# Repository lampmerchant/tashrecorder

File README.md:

# TashRecorder

## Elevator Pitch

It's an audio interface that can be switched between imitating the Farallon MacRecorder, an audio digitizer for vintage Macintosh computers without audio input, and the Apple MIDI Interface, a standard MIDI interface for the Macintosh.  It targets the PIC12F1501 (8 pins, ~$0.96) microcontroller.

## Technical Details

### Connections

```
                      .--------.
              Supply -|01 \/ 08|- Ground
       RxD- <--- RA5 -|02    07|- RA0 <--- MIDI/Audio In
       RxD+ <--- RA4 -|03    06|- RA1 ---> Clock Out
Mode Select ---> RA3 -|04    05|- RA2 ---> LED
                      '--------'
```

Mode Select floats high and selects audio digitizer mode by default; pulling it low selects MIDI interface mode.  The mode can be changed at any time.

The LED output is active high.

### Audio Digitizer Mode

In Audio Digitizer mode, the firmware imitates a Farallon MacRecorder, generating a clock of approximately 358 kHz (one tenth the NTSC color burst frequency), oversampling the input pin at a rate of approximately 44 kHz and transmitting 8-bit samples to the Macintosh at a rate of approximately 22 kHz.

The LED flashes on when the audio has peaked for a set number of consecutive samples (3 by default, changeable by editing the PEAKPWR parameter in firmware).  Peaking is determined by masking off a number of bits (3 by default, changeable by editing the PEAKMSK parameter in firmware) and checking whether the remaining bits are all ones or all zeroes.

### MIDI Interface Mode

In MIDI Interface Mode, the firmware imitates the input of an Apple MIDI Interface, generating a 1 MHz clock (32 times the MIDI baud rate of 31250 Hz) and relaying the input pin's state directly to the RxD pins.  The MIDI input pin's state is inverted before being reflected by the RxD pins; this allows it to be connected directly to the output of an optocoupler such as the 6N138 with the addition of an external pullup resistor.

The LED flashes on when data is being received over the MIDI interface.

### Building Firmware

Building the firmware requires Microchip MPASM, which is included with their development environment, MPLAB.  Note that you **must** use MPLAB X version 5.35 or earlier or MPLAB 8 as later versions of MPLAB X have removed MPASM.

The firmware can also be built using gpasm, an MPASM-compatible assembler that is part of the [gputils](https://gputils.sourceforge.io/) project.  Please note, however, that the release builds are built using MPASM and compatibility with gpasm is not tested.

## Building Your Own

1-Bit Fever Dreams on YouTube has made a helpful [video](https://www.youtube.com/watch?v=QnrPvtYhGZ4) detailing the process of building a TashRecorder using [demik's PCB](https://github.com/lampmerchant/tashrecorder/tree/main/pcb).

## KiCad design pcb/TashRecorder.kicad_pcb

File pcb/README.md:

# TashRecorder

This is a simple (but dense) design, using all through hole components.  It's designed this way to be period correct and easy to build for people who don't like soldering SMT components.

This folder contains the source KiKad files for the main board. Please check the Panels subfolder for the FR-4 front and back plates.

## BOM
### Mandatory

Here is the BOM for the main board. Part number are what was tested on prototypes board but you may find alternatives easily, especially resistors and sockets

| Reference(s)          | Value      | Quantity | Notes                                  | Part number              |
|-----------------------|------------|----------|----------------------------------------|--------------------------|
| C1, 2, 7, 9-10, 12-13 | 100nF      | 7        | ceramic capacitor 5.08mm               | Weltron 453358           |
| C3                    | 6800pF     | 1        | film capacitor 5mm                     | Wima FKS2G016801B00KSSD  |
| C8                    | 680pF      | 1        | film capacitor 5mm                     | Wima FKP2J006801D00HSSD  |
| C4, C5, C8, C11       | 22uF       | 4        | aluminium electrolytic capacitor       | Panasonic ECA-1HHG220I   |
| D1 to D6              | 1N4148     | 6        | general purpose switching diode        | Vishay 1N4148-TAP        |
| D7                    | Red        | 1        | High efficiency 20000-30000mcd 5mm LED | TRU TC-10551696          |
| J1                    | RCA        | 1        | RCA Phono Connector                    | CUI Devices RCJ-013      |
| J2                    | Connector  | 1        | Circular Mini-DIN Connectors 8P        | Kycon KMDGX-8S-AS        |
| MK1                   | Micro      | 1        | omnidirectional electret microphone    | DB Unlimited MO093803-1  |
| R1, R2, R6            | 2.4kΩ      | 3        | standard 0.25W metal film resistor     | TRU MF0W4FF2401          |
| R3, R12               | 1.2kΩ      | 2        | standard 0.25W carbon film resistor    | TRU CFR0W4J0122          |
| R4, R5, R7, R9        | 220kΩ      | 4        | standard 0.25W carbon film resistor    | TRU CFR0W4J0224          |
| R8, R14, R15          | 47Ω        | 3        | standard 0.25W carbon film resistor    | TRU CFR0W4J0470          |
| R10                   | 4.7kΩ      | 1        | standard 0.25W carbon film resistor    | TRU CFR0W4J0472          |
| R11                   | 10kΩ       | 1        | standard 0.25W carbon film resistor    | TRU CFR0W4J0103          |
| RV1                   | 100kΩ      | 1        | audio 100kΩ panel potentiometer        | Bourns PTD901-2015K-A104 |
| SW1                   | SPDT       | 1        | slide switches right angle             | E-Switch EG1224          |
| U1, U2                | 2.5V       | 2        | 2.5V TO-92-3 20mA voltage reference    | ON Semi LM385Z-2.5       |
| U3                    | OPA2337    | 1        | low power RR out CMOS op-amp           | Texas OPA2337PA          |
| U4                    | PIC        | 1        | 8-bit Microcontrollers DIP PIC12F1501  | MC PIC12F1501-I/P        |
| Case                  | ABS        | 1        | Instrument Case, ABS 2.6x2.6"          | HM 1593K(TBU\|GY\|BK)    |
| PCB Screws            | #4         | 4        | Phillips Pan Head screws #4 x 1/4"     | SERPAC 6004              |
| Socket                | DIP-8      | 2        | DIP-8 socket                           | TRU TC-A 08-LC-TT-203    |
| Knob                  | Blue       | 1        | knob for Ø 6 mm 18 teeth shafts        | PSP 49009-BL             |

Using sockets is recommended because it will allow you to reclaim the microcontroler and op-amp. This will also allow you to upgrade the firmware if a future firmware is released.

### BOM (external links)
Here is a complete mouser. It includes lots of 10 when that was cheaper. You may have extra components
- https://www.mouser.fr/ProjectManager/ProjectDetail.aspx?AccessID=31409f3429

## PCBs
Main PCB is 4 layers. Panels are simple 2 layers boards. The gerbers are avaible in the release section.
Check for the following files:
* TashRecorder_2.1.zip: main board revision 2.1
* TashRecorder_back_panel_2.1.zip: FR-4 back panel revision 2.1
* TashRecorder_front_panel_2.1.zip: FR-4 front panel revision 2.1

You should be use any mainstream PCB manufacturer for theses. Nothing special about them. PCB thickness should be 1.6mm

On JLCPCB, select "Specify a location" to the option "Remove Order Number" for all of them

## Building
Building is straightworfard. It's recommended to start with small components first (diodes, then resistor, LED), then other components, and connectors last.
For Japanase mounted resistors, the resistor will go on the circle side

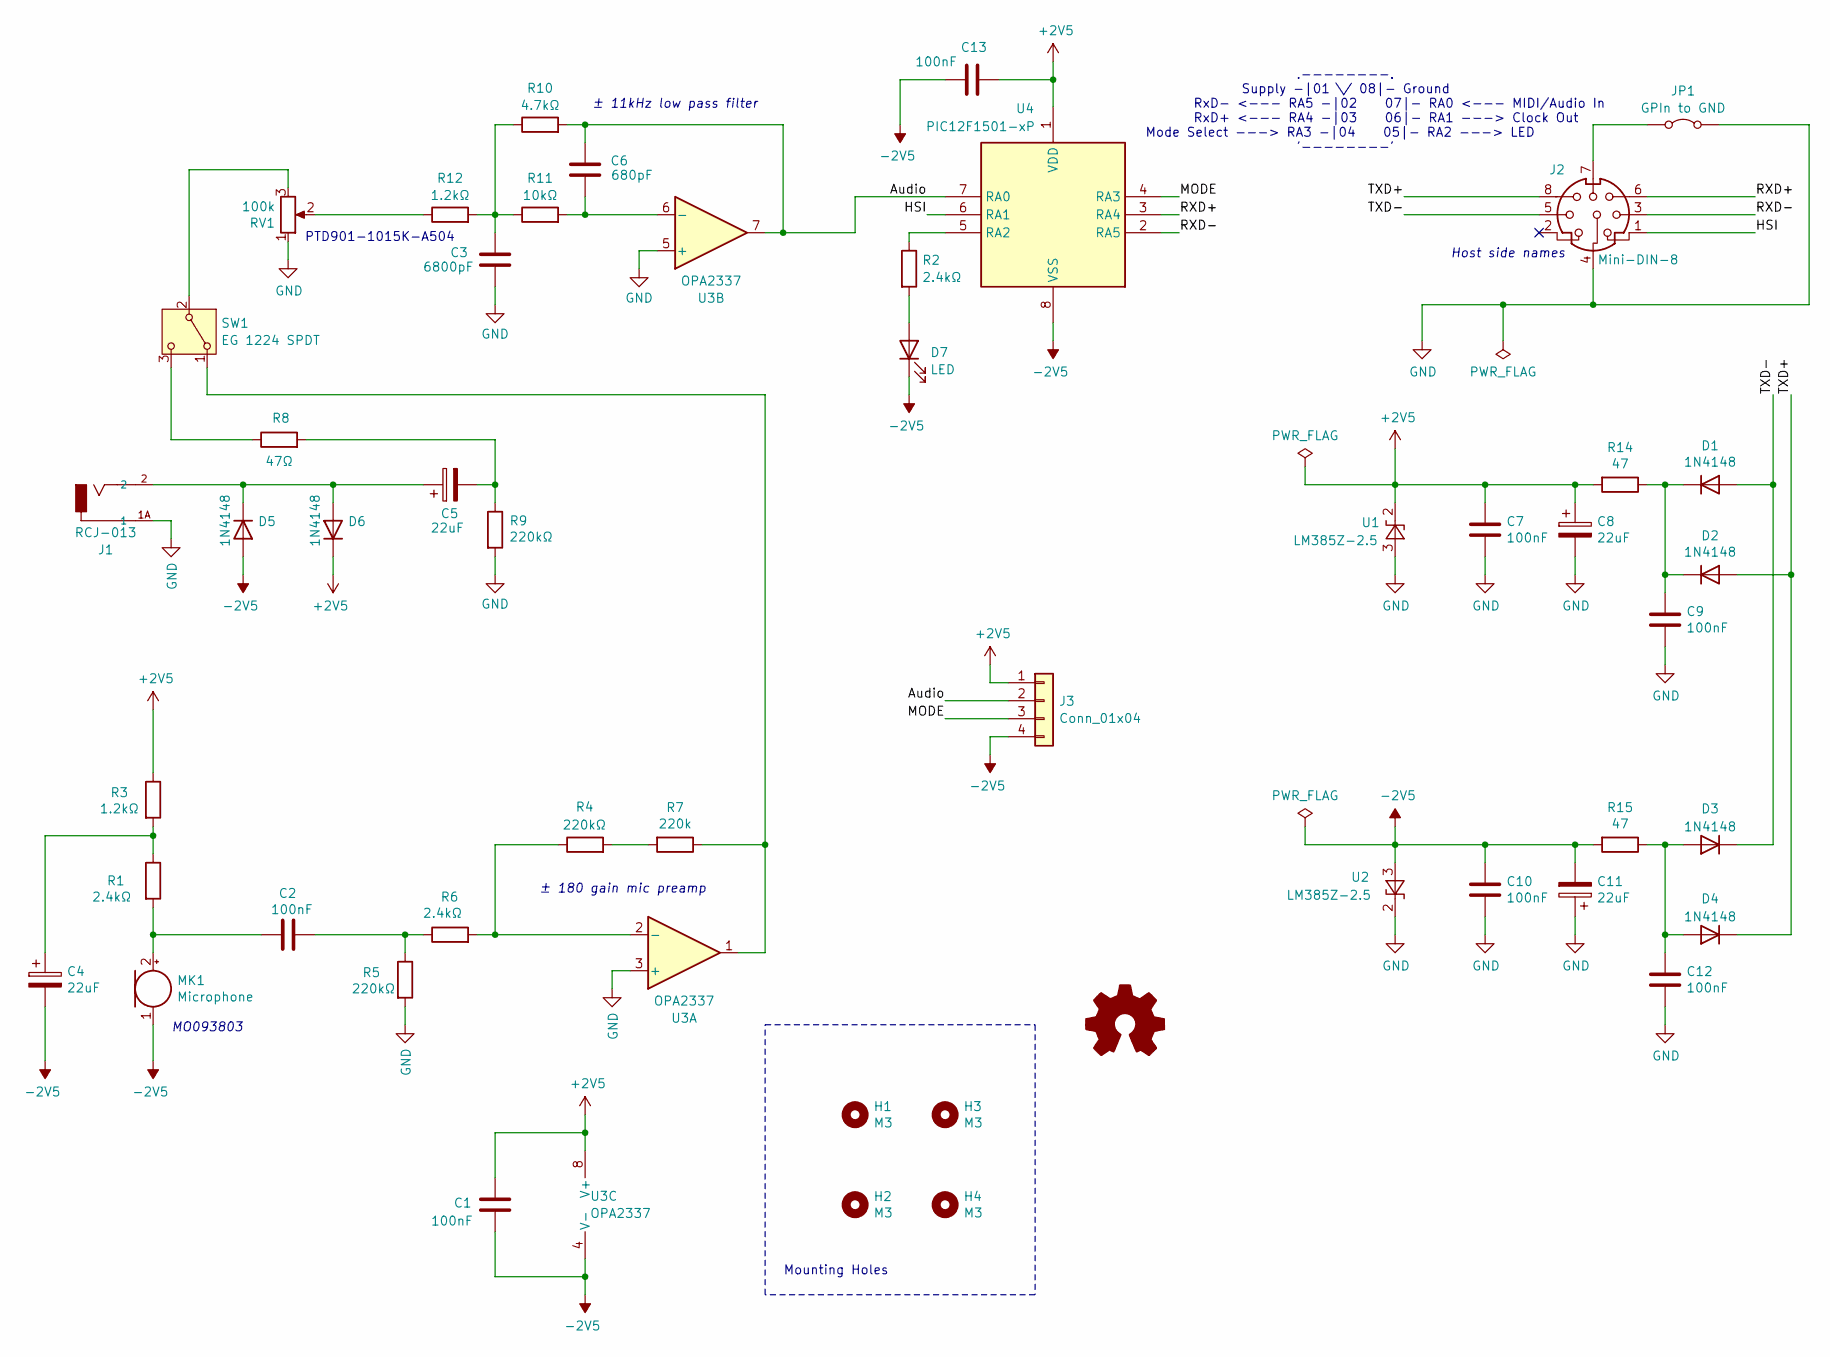
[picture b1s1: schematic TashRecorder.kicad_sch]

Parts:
C1, C2, C7, C9, C10, C12, C13: 100nF; C_Disc_D4.3mm_W1.9mm_P5.00mm
C3: 6800pF; C_Rect_L7.2mm_W4.5mm_P5.00mm_FKS2_FKP2_MKS2_MKP2
C4, C5, C8, C11: 22uF; CP_Radial_D5.0mm_P2.50mm
C6: 680pF; C_Rect_L7.2mm_W4.5mm_P5.00mm_FKS2_FKP2_MKS2_MKP2
D1, D2, D3, D4, D5, D6: 1N4148; D_DO-35_SOD27_P7.62mm_Horizontal
D7: LED; LED_D5.0mm_Horizontal_O6.35mm_Z9.0mm
H1, H2, H3, H4: M3; MountingHole_3.2mm_M3_Pad
J1: RCJ-013; CUI_RCJ-013; PART_REV B
J2: Mini-DIN-8; 57492681
J3: Conn_01x04; PinHeader_1x04_P2.54mm_Vertical
JP1: GPIn to GND; SolderJumper-2_P1.3mm_Open_Pad1.0x1.5mm
MK1: Microphone; CMA4544PFW
R1, R2: 2.4kΩ; R_Axial_DIN0207_L6.3mm_D2.5mm_P7.62mm_Horizontal
R3: 1.2kΩ; R_Axial_DIN0207_L6.3mm_D2.5mm_P7.62mm_Horizontal
R4, R5, R9: 220kΩ; R_Axial_DIN0207_L6.3mm_D2.5mm_P2.54mm_Vertical
R6: 2.4kΩ; R_Axial_DIN0207_L6.3mm_D2.5mm_P2.54mm_Vertical
R7: 220k; R_Axial_DIN0207_L6.3mm_D2.5mm_P2.54mm_Vertical
R8: 47Ω; R_Axial_DIN0207_L6.3mm_D2.5mm_P7.62mm_Horizontal
R10: 4.7kΩ; R_Axial_DIN0207_L6.3mm_D2.5mm_P2.54mm_Vertical
R11: 10kΩ; R_Axial_DIN0207_L6.3mm_D2.5mm_P2.54mm_Vertical
R12: 1.2kΩ; R_Axial_DIN0207_L6.3mm_D2.5mm_P2.54mm_Vertical
R14, R15: 47; R_Axial_DIN0207_L6.3mm_D2.5mm_P2.54mm_Vertical
RV1: 100k; PTD9011015FA203
SW1: EG 1224 SPDT; EG1224
U1, U2: LM385Z-2.5; TO-92_HandSolder
U3: OPA2337; DIP-8_W7.62mm_LongPads
U4: PIC12F1501-xP; DIP-8_W7.62mm_LongPads

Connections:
+2V5: C1.1, C7.1, C8.1, C13.1, D6.1 (K), J3.1, R3.1, R14.2, U1.2 (K), U3.8 (V+), U4.1 (VDD)
-2V5: C1.2, C4.2, C10.1, C11.2, C13.2, D5.2 (A), D7.1 (K), J3.4, MK1.1 (-), R15.2, U2.3 (A), U3.4 (V-), U4.8 (VSS)
/Audio: C6.2, J3.2, R10.2, U3.7, U4.7 (RA0)
/HSI: J2.1, U4.6 (RA1)
/MODE: J3.3, U4.4 (RA3)
/RXD+: J2.6, U4.3 (RA4)
/RXD-: J2.3, U4.2 (RA5)
/TXD+: D2.2 (A), D4.1 (K), J2.8
/TXD-: D1.2 (A), D3.1 (K), J2.5
GND: C3.2, C7.2, C8.2, C9.2, C10.2, C11.1, C12.2, J1.1A (1), J2.4, JP1.2 (B), R5.2, R9.2, RV1.1, U1.3 (A), U2.2 (K), U3.3 (+), U3.5 (+)
unnamed: C2.2, R5.1, R6.1
unnamed: C3.1, R10.1, R11.1, R12.2
unnamed: C4.1, R1.1, R3.2
unnamed: C5.2, R8.2, R9.1
unnamed: C9.1, D1.1 (K), D2.1 (K), R14.1
unnamed: C12.1, D3.2 (A), D4.2 (A), R15.1
unnamed: C5.1, D5.1 (K), D6.2 (A), J1.2
unnamed: D7.2 (A), R2.2
unnamed: J2.7, JP1.1 (A)
unnamed: C2.1, MK1.2 (+), R1.2
unnamed: R4.2, R7.2
unnamed: R12.1, RV1.2
unnamed: R7.1, SW1.1 (A), U3.1
unnamed: RV1.3, SW1.2 (B)
unnamed: R8.1, SW1.3 (C)
unnamed: R4.1, R6.2, U3.2 (-)
unnamed: C6.1, R11.2, U3.6 (-)
unnamed: R2.1, U4.5 (RA2)

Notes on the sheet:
.--------. Supply -|01 \/ 08|- Ground RxD- <--- RA5 -|02 07|- RA0 <--- MIDI/Audio In RxD+ <--- RA4 -|03 06|- RA1 ---> Clock Out Mode Select ---> RA3 -|04 05|- RA2 ---> LED '--------'
± 11kHz low pass filter
PTD901-1015K-A504
± 180 gain mic preamp
MO093803
Mounting Holes
Host side names

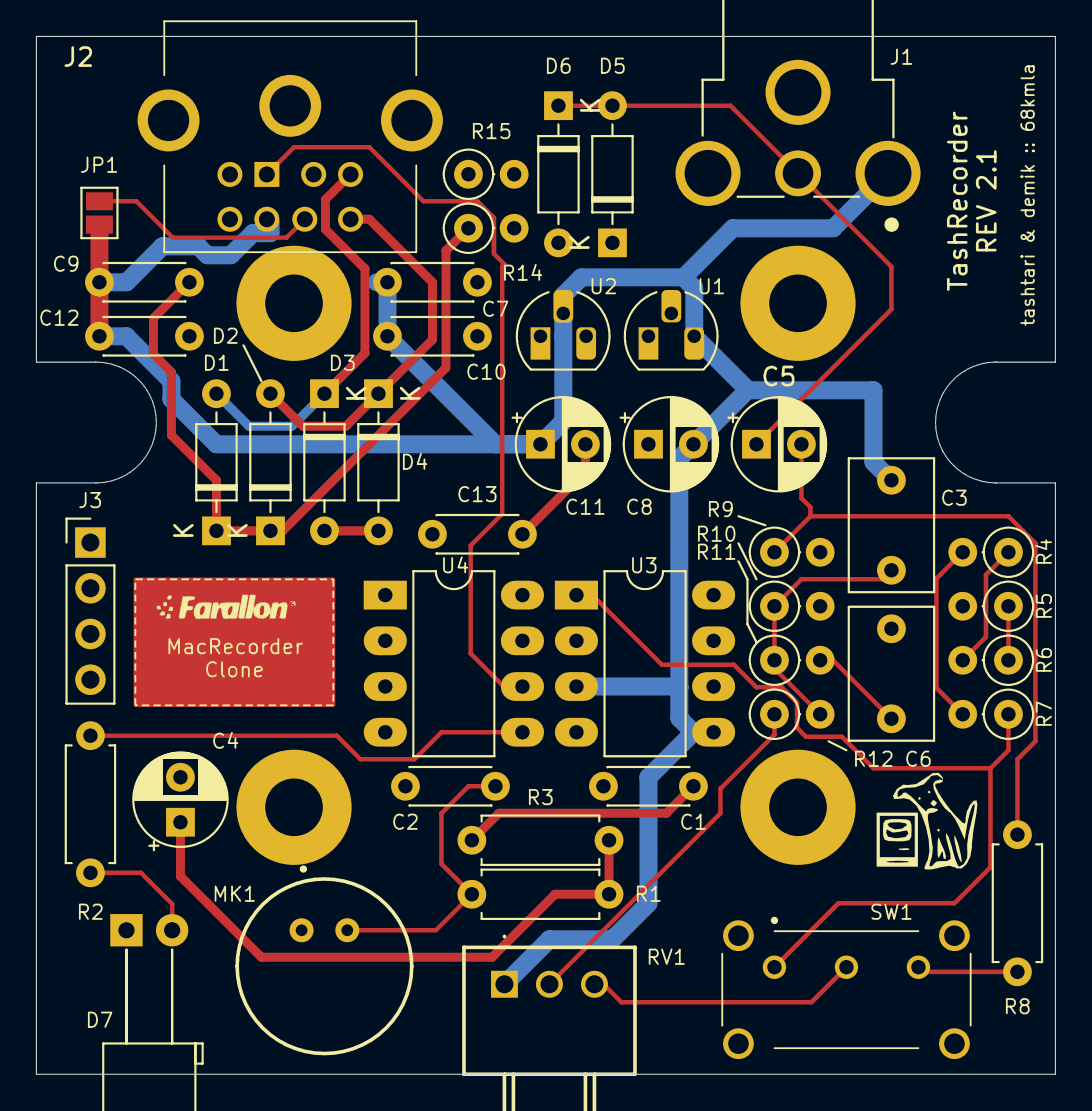
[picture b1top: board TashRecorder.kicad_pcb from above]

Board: 4 copper layers, 56.6 x 57.7 mm, 51 parts (1 on the bottom side), 28 nets.

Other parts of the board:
GB: LOGO; Farallon
GF: LOGO; Farallon

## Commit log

2024-04-24 20240424
2024-04-24 20240424-2
2024-05-06 20240506
2024-05-07 20240507
2024-05-22 20240522
2024-05-23 20240523
2024-06-02 20240602
2024-06-02 update peak parameter documentation
2024-06-02 20240602-2
2024-06-13 added PCBs
2024-06-13 added schematic in PDF form
2024-06-14 cleaned BOM
2024-06-14 added PCB Readme (BOM, mouser link)
2026-05-30 mention gputils as potential build tool
